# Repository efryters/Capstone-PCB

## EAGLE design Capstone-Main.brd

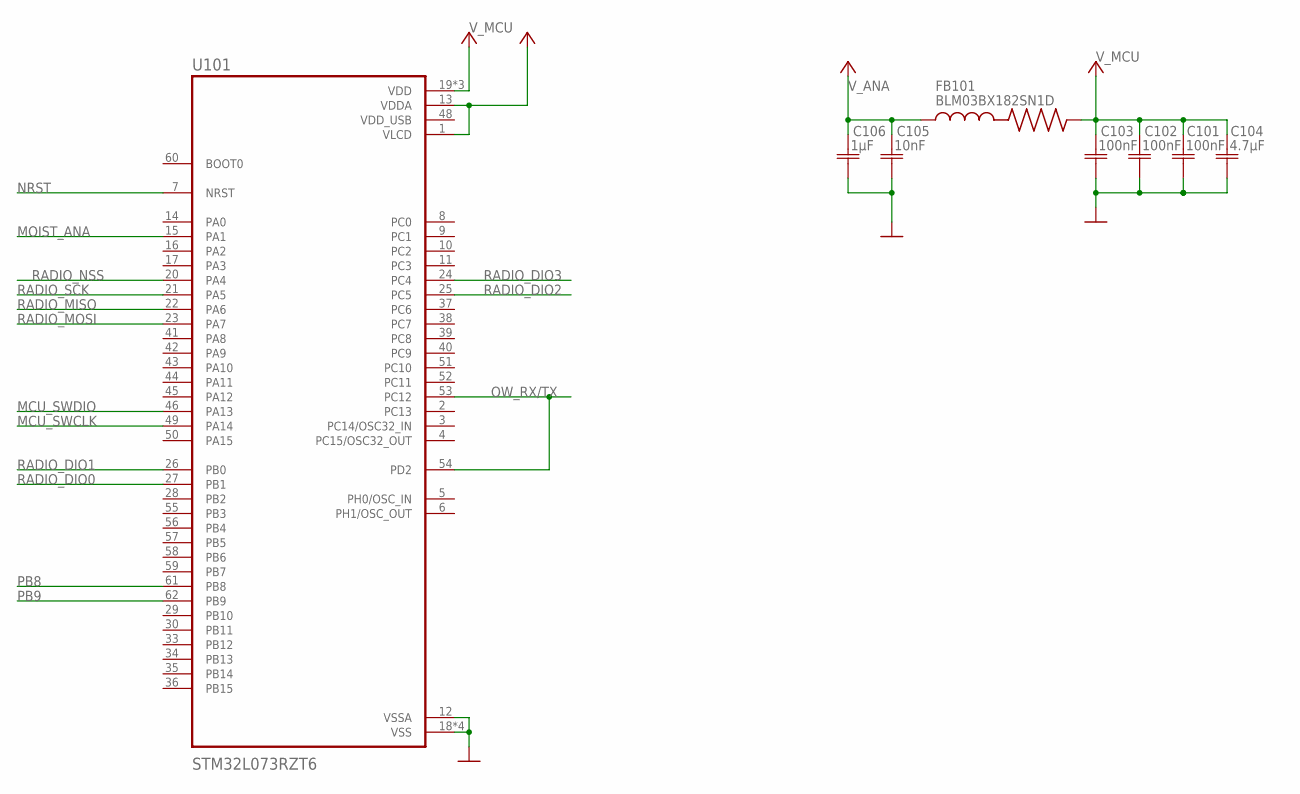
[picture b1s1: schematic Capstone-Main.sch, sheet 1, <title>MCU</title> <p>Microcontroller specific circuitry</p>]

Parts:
C101, C102, C103: 100nF; CAPC1608X85N
C104: 4.7μF; CAPC1608X85N
C105: 10nF; CAPC1608X85N
C106: 1μF; CAPC1608X85N
FB101: BLM03BX182SN1D; BEADC0603X33N
U101: STM32L073RZT6; QFP50P1200X1200X160-64N

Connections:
GND: C101.1 (C1), C102.1 (C1), C103.1 (C1), C104.1 (C1), C105.1 (C1), C106.1 (C1), U101.12 (VSSA), U101.18 (VSS), U101.31 (VSS), U101.47 (VSS), U101.63 (VSS); also elsewhere on the board
MCU_SWCLK: U101.49 (PA14); also elsewhere on the board
MCU_SWDIO: U101.46 (PA13); also elsewhere on the board
MOIST_ANA: U101.15 (PA1); also elsewhere on the board
NRST: U101.7 (NRST); also elsewhere on the board
OW_RX/TX: U101.53 (PC12), U101.54 (PD2); also elsewhere on the board
PB8: U101.61 (PB8); also elsewhere on the board
PB9: U101.62 (PB9); also elsewhere on the board
RADIO_DIO0: U101.27 (PB1); also elsewhere on the board
RADIO_DIO1: U101.26 (PB0); also elsewhere on the board
RADIO_DIO2: U101.25 (PC5); also elsewhere on the board
RADIO_DIO3: U101.24 (PC4); also elsewhere on the board
RADIO_MISO: U101.22 (PA6); also elsewhere on the board
RADIO_MOSI: U101.23 (PA7); also elsewhere on the board
RADIO_NSS: U101.20 (PA4); also elsewhere on the board
RADIO_SCK: U101.21 (PA5); also elsewhere on the board
VDD_USB: U101.48 (VDD_USB)
V_ANA: C105.2 (C2), C106.2 (C2), FB101.1, U101.1 (VLCD), U101.13 (VDDA)
V_MCU: C101.2 (C2), C102.2 (C2), C103.2 (C2), C104.2 (C2), FB101.2, U101.19 (VDD), U101.32 (VDD), U101.64 (VDD); also elsewhere on the board

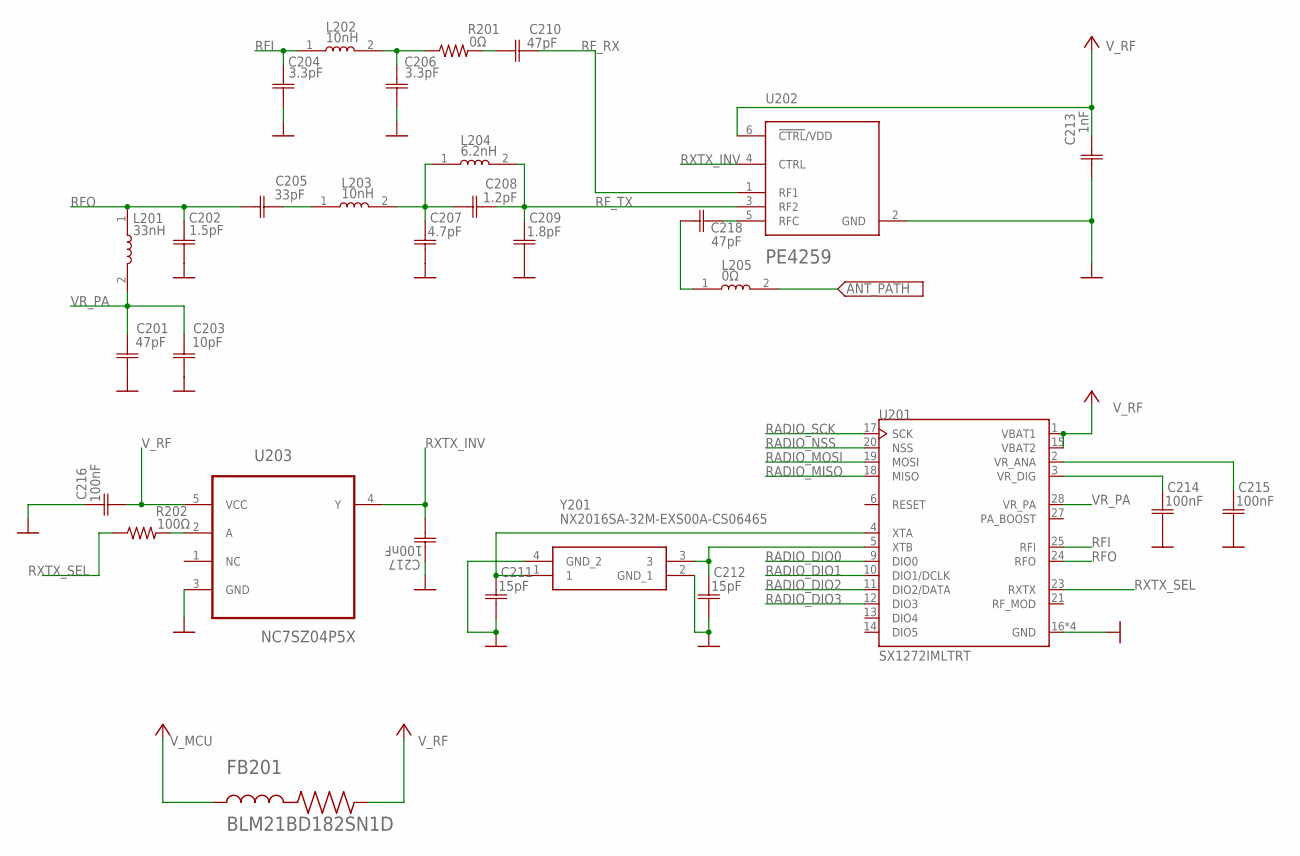
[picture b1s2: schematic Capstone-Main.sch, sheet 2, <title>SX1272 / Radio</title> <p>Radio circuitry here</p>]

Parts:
C201, C210, C218: 47pF; CAPC1608X85N
C202: 1.5pF; CAPC1608X85N
C203: 10pF; CAPC1608X85N
C204, C206: 3.3pF; CAPC1608X85N
C205: 33pF; CAPC1608X85N
C207: 4.7pF; CAPC1608X85N
C208: 1.2pF; CAPC1608X85N
C209: 1.8pF; CAPC1608X85N
C211, C212: 15pF; CAPC1608X85N
C213: 1nF; CAPC1608X85N
C214, C215, C216, C217: 100nF; CAPC1608X85N
FB201: BLM21BD182SN1D; BEADC2012X105N
L201: 33nH; INDC1608X95
L202, L203: 10nH; INDC1608X95
L204: 6.2nH; INDC1608X95
L205: 0Ω; INDC1608X95
R201: 0Ω; R0603
R202: 100Ω; R0603
U201: SX1272IMLTRT; QFN65P600X600X100-29N
U202: PEREGRINE_SEMICONDUCTOR_PE4259PEREGRINE_SEMICONDU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; PEREGRINE_SEMICONDUCTOR_PE4259_0
U203: NC7SZ04P5X; SOT65P210X110-5N
Y201: NX2016SA-32M-EXS00A-CS06465; NX2016SA32MEXS00ACS06465

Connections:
ANT_PATH: L205.2; also elsewhere on the board
GND: C201.1 (C1), C202.2 (C2), C203.1 (C1), C204.2 (C2), C206.2 (C2), C207.2 (C2), C209.2 (C2), C211.2 (C2), C212.2 (C2), C213.2 (C2), C214.2 (C2), C215.2 (C2), C216.1 (C1), C217.1 (C1), U201.16 (GND), U201.22 (GND), U201.26 (GND), U201.29 (GND), U202.2 (GND), U203.3 (GND), Y201.2 (GND_1), Y201.4 (GND_2); also elsewhere on the board
unnamed: C214.1 (C1), U201.3 (VR_DIG)
unnamed: C215.1 (C1), U201.2 (VR_ANA)
unnamed: C211.1 (C1), U201.4 (XTA), Y201.1
unnamed: C206.1 (C1), L202.2, R201.1
unnamed: C210.2 (C2), R201.2
unnamed: C212.1 (C1), U201.5 (XTB), Y201.3
unnamed: C205.1 (C1), L203.1
unnamed: C207.1 (C1), C208.1 (C1), L203.2, L204.1
unnamed: R202.2, U203.2 (A)
unnamed: C218.2 (C2), U202.5 (RFC)
unnamed: C218.1 (C1), L205.1
RADIO_DIO0: U201.9 (DIO0); also elsewhere on the board
RADIO_DIO1: U201.10 (DIO1/DCLK); also elsewhere on the board
RADIO_DIO2: U201.11 (DIO2/DATA); also elsewhere on the board
RADIO_DIO3: U201.12 (DIO3); also elsewhere on the board
RADIO_MISO: U201.18 (MISO); also elsewhere on the board
RADIO_MOSI: U201.19 (MOSI); also elsewhere on the board
RADIO_NSS: U201.20 (NSS); also elsewhere on the board
RADIO_SCK: U201.17 (SCK); also elsewhere on the board
RFI: C204.1 (C1), L202.1, U201.25 (RFI)
RFO: C202.1 (C1), C205.2 (C2), L201.1, U201.24 (RFO)
RF_RX: C210.1 (C1), U202.1 (RF1)
RF_TX: C208.2 (C2), C209.1 (C1), L204.2, U202.3 (RF2)
RXTX_INV: C217.2 (C2), U202.4 (CTRL), U203.4 (Y)
RXTX_SEL: R202.1, U201.23 (RXTX)
VR_PA: C201.2 (C2), C203.2 (C2), L201.2, U201.28 (VR_PA)
V_MCU: FB201.1; also elsewhere on the board
V_RF: C213.1 (C1), C216.2 (C2), FB201.2, U201.1 (VBAT1), U201.15 (VBAT2), U202.6 (!CTRL!/VDD), U203.5 (VCC)

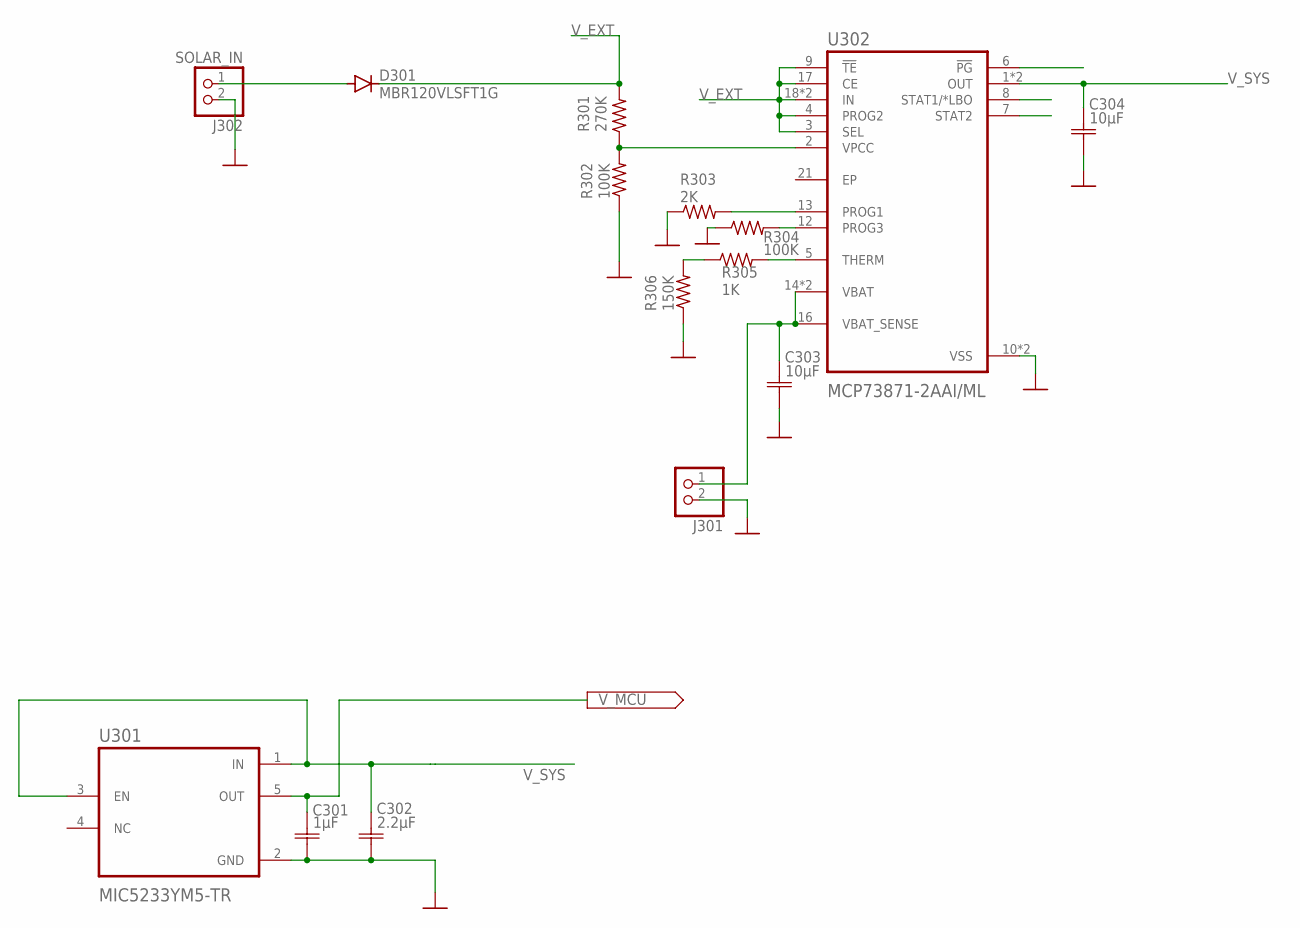
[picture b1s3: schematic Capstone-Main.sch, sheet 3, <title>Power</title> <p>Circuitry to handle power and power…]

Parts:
C301: 1μF; CAPC1608X85N
C302: 2.2μF; CAPC1608X85N
C303, C304: 10μF; CAPC1608X85N
D301: MBR120VLSFT1G; SOD-123_MINI-SMA
J301: JST_2PIN-SMT-RA; JST-PH-2-SMT-RA
J302: SOLAR_IN; JST-PH-2-SMT-RA
R301: 270K; R0603
R302, R304: 100K; R0603
R303: 2K; R0603
R305: 1K; R0603
R306: 150K; R0603
U301: MIC5233YM5-TR; SOT95P280X145-5N
U302: MCP73871-2AAI/ML; QFN50P400X400X100-21N

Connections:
GND: C301.2 (C2), C302.2 (C2), C303.2 (C2), C304.2 (C2), J301.2 (1), J302.2 (1), R302.1, R303.1, R304.1, R306.1, U301.2 (GND), U302.10 (VSS), U302.11 (VSS); also elsewhere on the board
unnamed: R301.1, R302.2, U302.2 (VPCC)
unnamed: R304.2, U302.12 (PROG3)
unnamed: R303.2, U302.13 (PROG1)
unnamed: C303.1 (C1), J301.1 (2), U302.14 (VBAT), U302.15 (VBAT), U302.16 (VBAT_SENSE)
unnamed: R305.1, R306.2
unnamed: R305.2, U302.5 (THERM)
unnamed: D301.A, J302.1 (2)
V_EXT: D301.C, R301.2, U302.3 (SEL), U302.4 (PROG2), U302.9 (!TE), U302.17 (CE), U302.18 (IN), U302.19 (IN); also elsewhere on the board
V_MCU: C301.1 (C1), U301.5 (OUT); also elsewhere on the board
V_SYS: C302.1 (C1), C304.1 (C1), U301.1 (IN), U301.3 (EN), U302.1 (OUT), U302.20 (OUT)

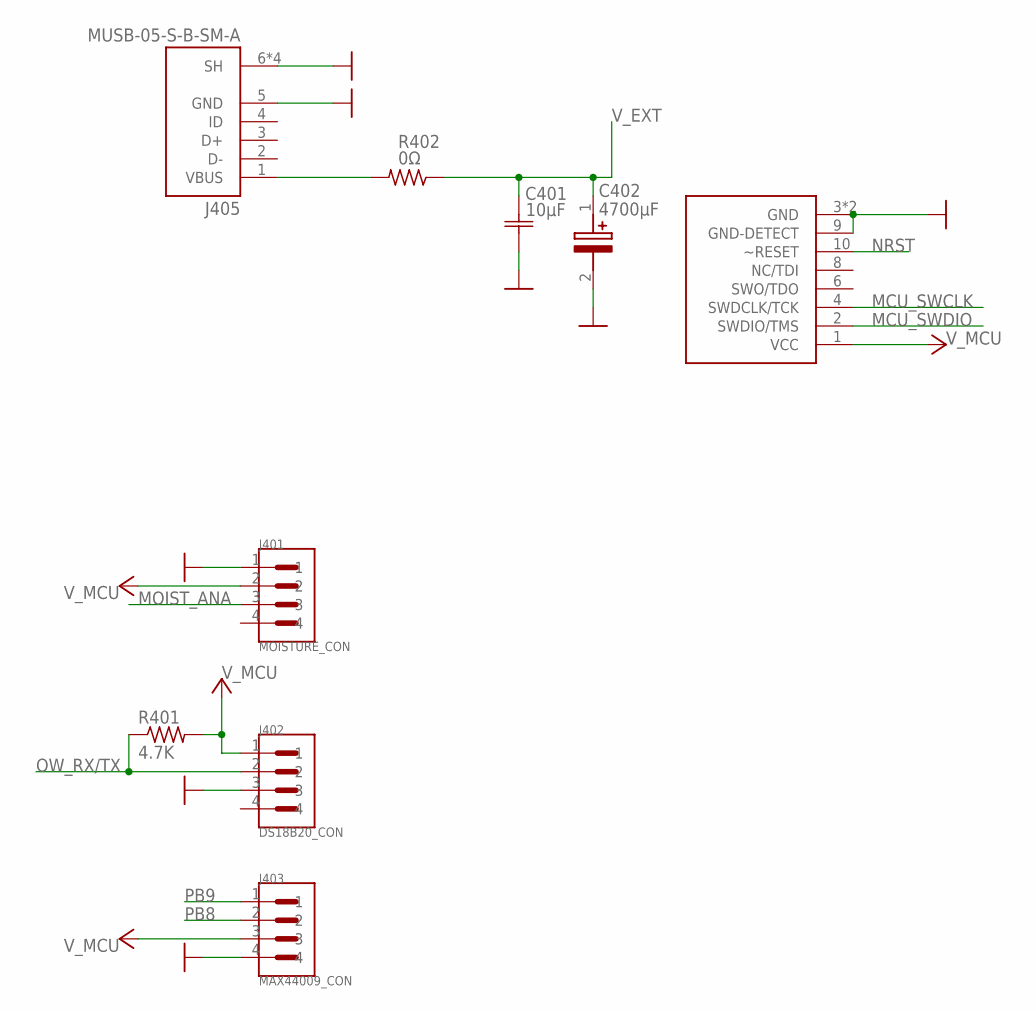
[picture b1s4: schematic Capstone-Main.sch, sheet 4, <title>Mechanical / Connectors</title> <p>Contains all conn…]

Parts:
C401: 10μF; CAPC1608X85N
C402: 4700μF; CAPAE1700X1700N
J401: MOISTURE_CON; JST_B4B-PH-SM4-TB
J402: DS18B20_CON; JST_B4B-PH-SM4-TB
J403: MAX44009_CON; JST_B4B-PH-SM4-TB
J404: 2X5_0.05"_CORTEX_DEBUGSMD_SHROUDED; 2X5_0.05"_SMD_SH
J405: MUSB-05-S-B-SM-A; SAMTEC_MUSB-05-S-B-SM-A
R401: 4.7K; R0603
R402: 0Ω; R0603

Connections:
GND: C401.1 (C1), C402.2 (-), J401.1, J402.3, J403.4, J404.3 (GND), J404.5 (GND), J404.9 (GND-DETECT), J405.5 (GND), J405.6 (SH), J405.7 (SH), J405.8 (SH), J405.9 (SH); also elsewhere on the board
MCU_SWCLK: J404.4 (SWDCLK/TCK); also elsewhere on the board
MCU_SWDIO: J404.2 (SWDIO/TMS); also elsewhere on the board
MOIST_ANA: J401.3; also elsewhere on the board
unnamed: J405.1 (VBUS), R402.2
NRST: J404.10 (~RESET); also elsewhere on the board
OW_RX/TX: J402.2, R401.1; also elsewhere on the board
PB8: J403.2; also elsewhere on the board
PB9: J403.1; also elsewhere on the board
V_EXT: C401.2 (C2), C402.1 (+), R402.1; also elsewhere on the board
V_MCU: J401.2, J402.1, J403.3, J404.1 (VCC), R401.2; also elsewhere on the board

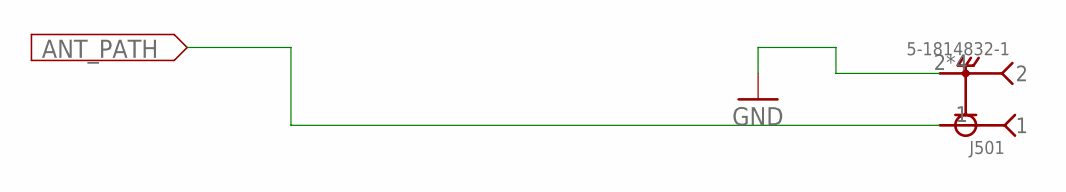
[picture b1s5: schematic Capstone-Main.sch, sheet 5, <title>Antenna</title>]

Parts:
J501: 5-1814832-1; TE_5-1814832-1

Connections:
ANT_PATH: J501.1; also elsewhere on the board
GND: J501.2, J501.3 (2), J501.4 (2), J501.5 (2); also elsewhere on the board

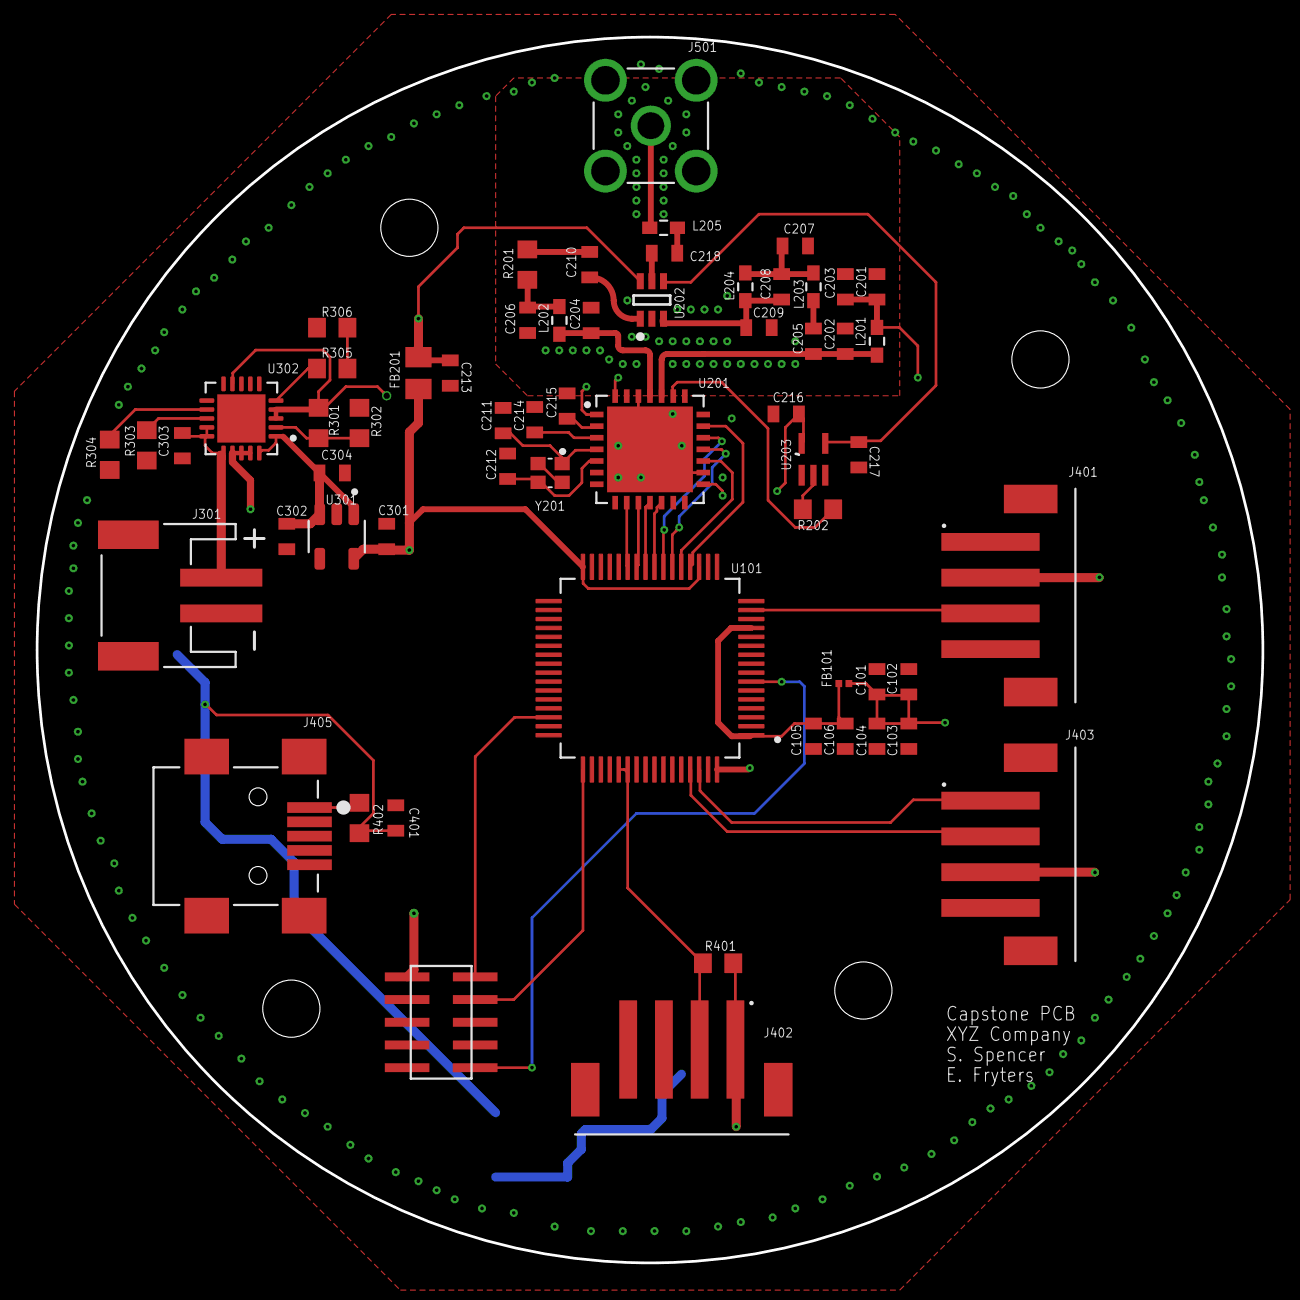
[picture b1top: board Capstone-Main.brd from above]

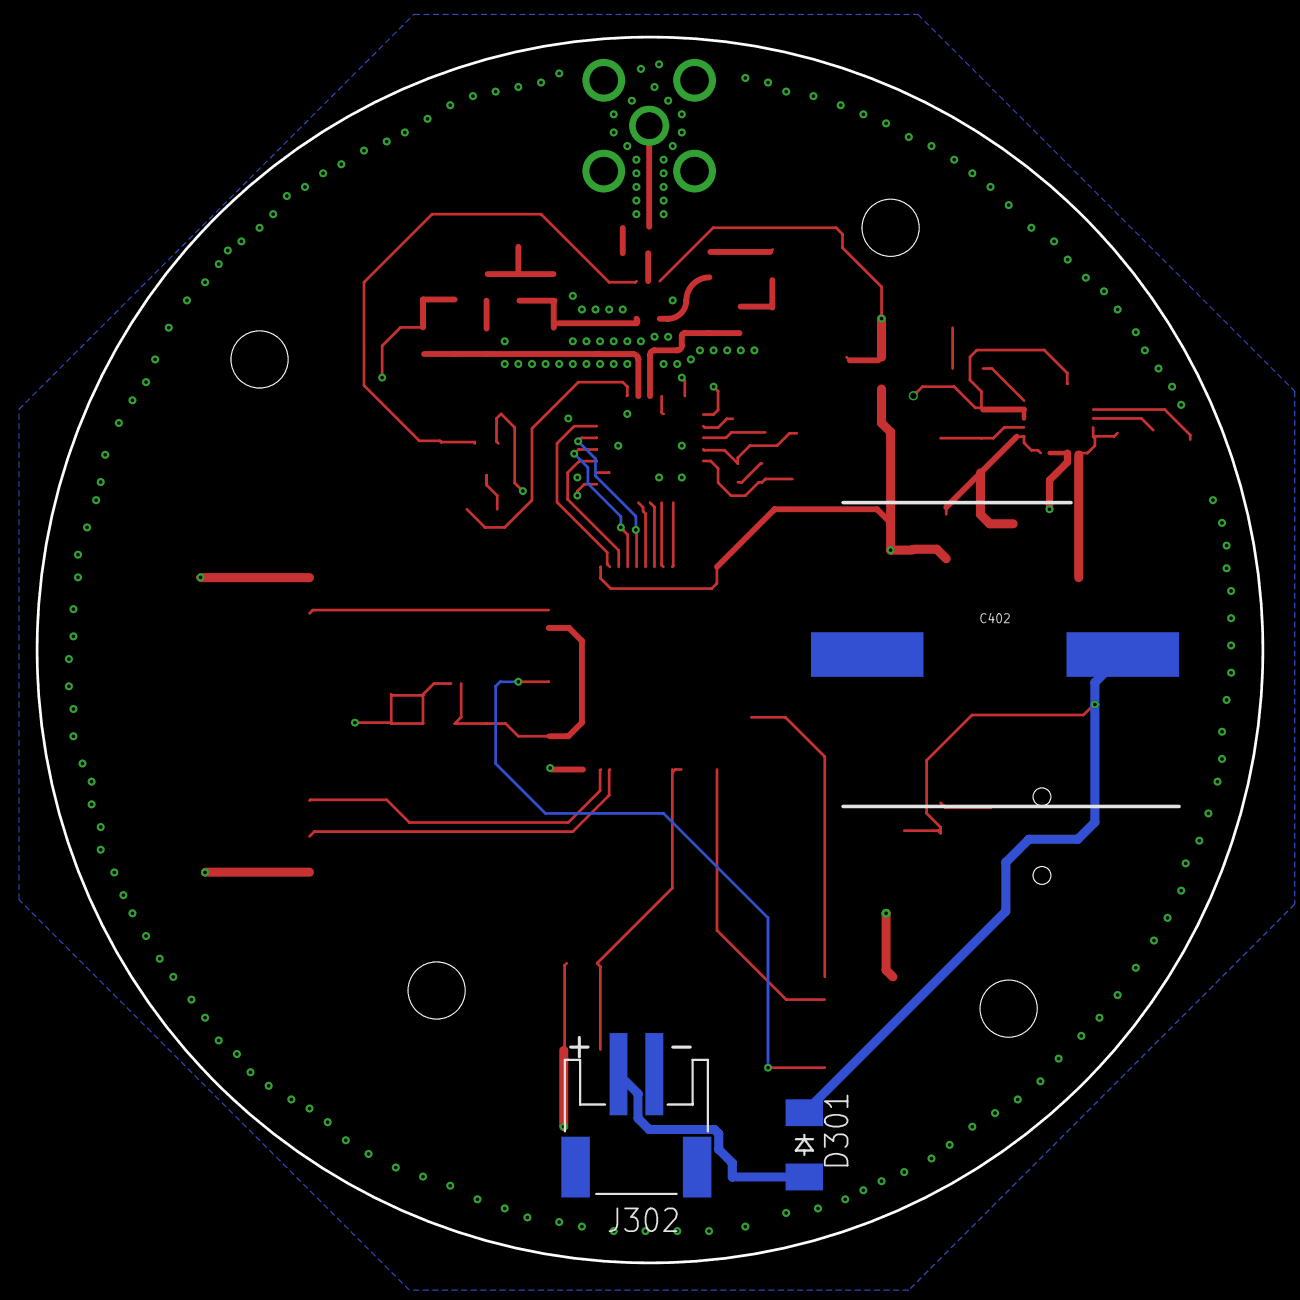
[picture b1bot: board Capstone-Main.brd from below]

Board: 4 copper layers, 68.6 x 68.6 mm, 63 parts (3 on the bottom side), 48 nets.

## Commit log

2020-01-16 Modified net names, rearranged components
2020-01-20 Rearranged refdes and components
2020-01-30 Squash weird commits
    Rearranged components
    Added missing lib files
    Added missing lib files
2020-01-30 Adding charging IC and supporting components
2020-02-12 Updated stuff
2020-02-27 completed routing, to be reviewed
2020-03-08 Added solar charger port, fixed some issues.
2020-04-16 Create LICENSE
